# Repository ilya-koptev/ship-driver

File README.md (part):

# ship-driver

`ship-driver` — самодельный драйвер корабельной шины для контроллеров **Wiren Board**. Он берёт
под себя все четыре LoRa‑передатчика (`/dev/ttyMOD1..4`) — это четыре независимых равнозначных
канала. На каждом работает своя копия одного и того же «автомата корабля»: опрашивает борт по
Modbus (модули `pwm8a04` на адресах 11/12/13 и ИБП `WB‑UPS‑v3` на адресе 10), подмешивает в шину
команды плеера DFPlayer, ведёт машину режимов, держит расписание опроса и снижает ток заряда,
когда батарея греется. Всё, что происходит на борту, видно в MQTT — как устройства `boat1..4`.

Кроме кораблей драйвер обслуживает **беспроводные зарядные станции** `charger1..N`: включает реле
передатчика и магнитов фиксации, следит за током передатчика. С зарядками он общается по Modbus
RTU через TCP‑шлюз (EBYTE serial server) — отдельно от корабельной LoRa‑шины.

На корабельной шине он заменяет собой штатные `wb-mqtt-serial` и `rs485-arbiter`.

**Дальше — два больших раздела, под две разные задачи:**

- **[🛰 Удалённое управление по MQTT](#-удалённое-управление-по-mqtt)** — если вы управляете
  кораблём и зарядками из стороннего софта или с дашборда. Здесь только топики, контролы и
  команды; в железо вникать не нужно.
- **[🔧 Устройство, монтаж и настройка](#-устройство-монтаж-и-настройка)** — если вы собираете,
  ставите и настраиваете драйвер на контроллере: как он устроен, как всё подключено, конфиг,
  установка, выпуск релиза.

Полная спецификация MQTT с примерами лежит в **[`MQTT-API.md`](MQTT-API.md)**, а список компонентов
корабля (BOM) — в **[`BUILD.md`](BUILD.md)**.

---

# 🛰 Удалённое управление по MQTT

Здесь собрано всё, что нужно для удалённого управления — про железо и установку можно не думать.

**Как устроены топики.** Прочитать значение можно из `/devices/<устройство>/controls/<контрол>`, а
чтобы отдать команду — пишем в тот же топик с суффиксом `/on`. Устройств три вида: `boat1..4`
(корабли), `charger1..N` (зарядки) и `ship_setup` (проводная преднастройка — она относится к
разделу настройки).

## Корабли `boat1..4`

Устройство `boatN` появляется **только для реально подключённых каналов** — там, где есть порт
`/dev/ttyMODn` и LoRa‑модем отвечает. Состав борта всегда один и тот же: 4 мотора и 5 огней. Пока
канал не на связи (режим SEARCH) или выключен (OFF), на дашборде видны только `enabled`, `mode` и
`ship_number` — остальные контролы прячутся и возвращаются, как только борт выходит на связь.

| Контрол | Доступ | Назначение |
|---|---|---|
| `enabled` | зап. | канал вкл/выкл (1/0) |
| `mode` | чт. | текущий режим (см. ниже) |
| `battery_current` / `battery_voltage` / `battery_temperature` / `charge_level` | чт. | телеметрия ИБП |
| `input_voltage` | чт. | входное напряжение ИБП, В (опрос 5 с, вместе с током) |
| `rssi` / `comms_errors` / `link_quality` | чт. | качество LoRa‑связи активного борта: RSSI (дБм), промахов чтения за 5 мин, % успешных чтений |
| `link_score` | чт. | **общая оценка связи 0…100** — свёртка потерь, качества, сигнала и задержки в одно число (см. «Оценка связи») |
| `read_failures` | чт. | **реально потерянные чтения** за 5 мин — отказы после всех повторов (в отличие от `comms_errors`, где считается каждая попытка) |
| `err_timeout` / `err_frame` | чт. | подпись отказов за 5 мин: «не пришло ни байта» (потерян пакет) против «обрывок / чужой кадр / битый CRC» (фрейминг, тайминги) |
| `course` / `roll` / `pitch` | чт. | углы борта, ° — курс (−180…180), крен, дифферент (датчик считает их сам) |
| `gyro_x` / `gyro_y` / `gyro_z` | чт. | угловые скорости, °/с (`gyro_z` = скорость поворота по курсу) |
| `accel_x` / `accel_y` / `accel_z` | чт. | ускорения в системе борта, g (в них входит и проекция силы тяжести) |
| `mag_x` / `mag_y` / `mag_z` | чт. | магнитометр, сырые единицы — по ним видно искажения поля (моторы, магниты площадки) |
| `q0` … `q3` | чт. | кватернион ориентации (единичный) — для расчётов без разрывов и вырождений |
| `sensor_temp` | чт. | температура датчика, °C |
| `retry_fixed` / `lat_p95` | чт. | промахов, вылеченных повтором, и латентность чтения p95 (мс) |
| `back_left` / `front_left` / `back_right` / `front_right` | зап. | моторы (Back/Front × Left/Right), **0–100 делений газа**: 0 = выход снят, 1 = холостой (1000 мкс), 100 = полный (2000 мкс). Дробные принимаются |
| `nav_lights` / `deck_lights` / `cabin_light1` / `cabin_light2` | зап. | свет, 0–100 % |
| `morse_lamp` | зап. | **переключатель** морзянки: 1 — гонять текст по кругу, 0 — погасить |
| `mp3_track` | зап. | плеер: 0 = стоп, 1–15 = трек |
| `mp3_volume` | зап. | плеер: громкость 0–30 |
| `ship_number` | зап. | номер корабля (= LoRa‑адрес) — переключает канал на этот корабль и делает **полную реинициализацию** (холостой + переарм ESC, газ прежнего борта не наследуется) |

Частоты ШИМ, тока заряда и параметров LoRa (канал, air‑rate, мощность) на дашборде `boatN` нет —
всё это живёт в конфиге контроллера.

### Газ задаётся частотой, а не скважностью

Скважность модуль pwm8a04 принимает только целыми процентами, поэтому при 400 Гц шаг
импульса был 25 мкс — на четырёх моторах это заметные ступеньки хода. Теперь скважность
моторных каналов постоянна (`motor_duty`, 60 %), а газ несёт **частота**: импульс =
`motor_duty` · 1e4 / f. Деления 1…100 это 600…300 Гц и 10.1 мкс на деление; дробные
значения принимаются, железный предел около 2.4 мкс.

Ход ползунка **нелинейный**. Деление 1 — холостой (1000 мкс, ESC взведён, вал стоит),
деление 2 — `pulse_start_us` = 1047 мкс, **измеренная точка страгивания**, дальше до
`pulse_top_us` идёт степенная кривая `x**throttle_gamma`. При `gamma` = 1.5 шаг растёт от
1 мкс у страгивания до 15 мкс у полного газа, и рабочая зона до 1400 мкс занимает половину
ползунка (51 деление) вместо 37 при линейной шкале. `gamma` = 1.0 возвращает линейную.

Круче 1.5 идти бессмысленно: шаг импульса опускается ниже 1.67 мкс, которые железо различает
у холостого, и деления начинают давать одну и ту же частоту — ползунок растёт, управление нет.

Точка страгивания **измерена**, а не оценена: стенд 25.08 без винтов — на 1037 мкс один вал
дёргается (зацепление, не вращение), на 1042 крутятся два, на 1048 все четыре. Прежде деления
2…14 лежали внутри мёртвой зоны и не давали ничего. Разрыв между делениями 1 и 2 намеренный:
это стык «стоит / пошёл», дробные значения между ними смысла не имеют.

Оговорка: пороги четырёх моторов разъехались примерно на 10 мкс, поэтому у самого низа шкалы
два движителя тянут, а два ещё нет — на минимальном газу катер будет уводить. Пол общий на все
каналы; свой пол на канал это вылечило бы, но выбран общий.

### Датчик курса: «его нет» — только про ни разу не ответивший

Такой вывод драйвер делает **только** про датчик, который не ответил ни разу на этом
борту (`sensor_giveup` попыток, по умолчанию 10). Если он отвечал хоть раз — значит
стоит, и при отказах чтения показывается обычная ошибка `meta/error="r"`, а опрос
продолжается.

Признанный отсутствующим переспрашивается раз в `sensor_retry_s` (по умолчанию 60 с) и
**возвращается сам**, сняв пометку. Одна транзакция в минуту ничего не стоит.

Зачем так: 25.08 драйвер объявил отсутствующим датчик, отвечавший минутой раньше —
хватило трёх потерянных кадров подряд при RSSI −57 (чтение идёт без повтора, `tries=1`,
чтобы не занимать канал, поэтому потерянный кадр = неудача). Опрос выключился через 48 с
после старта, и плашка курса 26 минут горела красным с замороженными значениями. Вывод
был сильнее данных, порог низким, а отказ необратимым — исправлено всё три.

### Останов газа идёт через холостой, а не снятием сигнала

Деление 0 снимает сигнал совсем, а регулятор не может отличить «сигнала нет» от
«оборвался провод» — поэтому он выключается не по команде, а по своему
**failsafe-таймауту**, секундами позже. Наблюдение 25.08: после сброса в 0 вал
продолжал вращаться, при этом отказов записи скважности в журнале не было ни одного,
то есть запись проходила и дело было не в ней.

Поэтому останов двухшаговый:

1. сразу выдаётся **холостой импульс** (`motor_duty` на частоте холостого) — это явная
   команда «минимум», регулятор исполняет её немедленно и вал встаёт;
2. через `stop_idle_s` (по умолчанию 1 с) выход гасится совсем, и этот шаг
   **подтверждается чтением** регистра — «записал» и «стало нулём» это разные
   утверждения. Не подтвердилось — повтор до `stop_tries` раз.

Если подтвердить так и не удалось, в журнал идёт `ОСТАНОВ НЕ ПОДТВЕРЖДЁН`, на контроле
выставляется `meta/error="w"`, а мотор **остаётся на холостом импульсе**: выход не снят,
но вал стоит. Это безопаснее, чем настаивать на снятии сигнала.

### Морзянка на световом канале

Канал `morse_lamp` — **переключатель**, а не ползунок яркости. Включённый гоняет по кругу
текст из конфига, выключенный гасит лампу и возвращает каналу штатные 400 Гц.

Символ кодируется **шириной импульса** при низкой частоте: частота ставится один раз,
дальше на каждый символ идёт одна запись скважности. Форму вспышки держит сам модуль,
поэтому дрожание радиоканала сдвигает момент начала символа, но не портит его длину —
а если гонять частоту, на символ уходило бы две записи вместо одной.

По умолчанию: 2 Гц (период 500 мс), точка = скважность 20 (вспышка 100 мс), тире =
скважность 60 (300 мс), текст `AHOY`, цикл 22.5 с. Всё в `main.morse`:
`channel`, `text`, `hz`, `dot`, `dash`, `letter_gap`, `word_gap`, `cycle_gap`
(паузы — в периодах). Латиница и цифры; чего нет в таблице, пропускается.

**Минимум частоты у pwm8a04 — 1 Гц**, проверено записью и обратным чтением 25.08;
значение 65535 модуль записывать отказывается.

Такт даёт общий цикл канала (холостой шаг 0.05 с) — отдельного потока нет. Поэтому
телеметрия может сдвинуть начало символа на свою длительность, но не его ширину.

Полная реинициализация борта (новый корабль или ребут модуля) **гасит морзянку**: её
включали для прежнего борта, и продолжать мигать на новом было бы неверно. После
реконнекта без потери питания она продолжается, сама переставив свою частоту.

### Пол шкалы мерится на каждой установке

`pulse_start_us` — импульс на делении 2 — **переносу между установками не подлежит**.
На стенде без винтов вал шёл с 1047 мкс, а на борту 9 под нагрузкой деления 2…12 дали
ровную полку по току АКБ: мотор крутится на своих минимальных оборотах, и газ на них
не влияет. Рост начинался с 1080 мкс, туда и поставлен пол — полка исчезла, ток растёт
с деления 2 монотонно.

Мерить: `tools/thr-current.py --motor back_left` — ступенчатый проход газа с замером
`battery_current`. Ток объективнее глаз: пока вал стоит, ESC потребляет только на себя.
По одному мотору за прогон, иначе ток не отнести к движителю. `tools/thr-start.py` делает
то же на стенде, где тока нет, — подаёт кандидатов и ждёт, что вал увидят глазами.

Скрипты берут кривую **из конфига драйвера**, а не помнят числами: 25.08 версия с
зашитым полом печатала неверные импульсы сразу после его сдвига.

Порядок записи при смене частоты обязателен: **скважность 0 → частота → рабочая
скважность**. Иначе новая частота ложится на старую скважность и даёт выброс импульса —
на стенде так получился лишний пуск на 1675 мкс. Одиночная команда газа этого не требует:
рабочая скважность уже стоит, меняется только частота (один кадр, задержка как прежде).

Частота вне рабочей полосы означает «модуль потерял питание и вернулся к заводским
1000 Гц» → полная реинициализация с переармом ESC. Отказ идёт в безопасную сторону:
заводская частота выше полосы, значит импульс слишком короткий и моторы стоят.

**Конфиг допускает строки-комментарии `//`.** Раньше не допускал: `json.load` на них
падал, драйвер молча уходил в дефолты и печатал только невнятное `conf load err`.
Снимаются строки, которые целиком комментарий; `//` внутри значения остаётся.

```sh
mosquitto_pub -t /devices/boat1/controls/front_right/on -m 50   # мотор перёд-право = 50%
mosquitto_pub -t /devices/boat1/controls/nav_lights/on  -m 100  # ходовые огни = 100%
mosquitto_pub -t /devices/boat1/controls/mp3_track/on   -m 3    # играть трек 3
mosquitto_pub -t /devices/boat2/controls/ship_number/on -m 23   # канал 2 -> корабль №23 (сразу)
mosquitto_sub -t /devices/boat1/controls/mode                   # текущий режим
```

### Режимы (`mode`)

| Режим | Когда | Что делает |
|---|---|---|
| **SEARCH** | корабль не на связи | непрерывно зондирует эфир; поймал ответ → инициализация → рабочий режим |
| **SAILING** | пришла любая команда управления | сбрасывает таймер 30 с (команды плеера режим не меняют) |
| **CHARGING** | 30 с без команд и ток батареи > 0 | заряд идёт максимально быстро, но под контролем температуры (см. «Тепловой регулятор») |
| **IDLE** | 30 с без команд и ток ≤ 0 | дрейф на батарее |
| **OFF** | `enabled = 0` | порт закрыт, эфир не трогается |

Из любого режима драйвер уходит в **SEARCH**, как только корабль перестаёт отвечать (два промаха
подряд). По умолчанию все 4 канала включены; и состояние вкл/выкл, **и заданный `ship_number`**
переживают перезагрузку контроллера.

### Номер корабля (`ship_number`)

У всех кораблей на одной радио‑частоте Modbus‑адреса одинаковые, поэтому на канале в каждый момент
можно разговаривать только с одним бортом — какой именно, задаёт **номер корабля** (он же
LoRa‑адрес приёмника). Стоит записать новое значение в `ship_number`, и канал мгновенно
переключается на нужный корабль: драйвер прописывает адрес в модем, берёт из конфига разводку
моторов и света именно этого корабля и через короткий SEARCH **инициализирует его заново** (частота
ШИМ и холостой газ). Раньше без этого шага при двух кораблях на одном канале второй мог не получить
`FREQ` и холостой газ — и тогда его моторы не заводились, хотя свет работал.

### Матрица опроса (период чтения телеметрии)

| Параметр | SEARCH | SAILING | IDLE | CHARGING |
|---|---|---|---|---|
| Ток батареи + вх. напряжение ИБП | ~0.8 с | 2 с | 5 с | 5 с |
| Температура АКБ | — | 60 с | 60 с | 10 с |
| Процент заряда | — | 60 с | 60 с | 20 с |
| Моторы + свет (обратная сверка, блочное чтение) | — | 30 с | 60 с | 30 с |
| Проверка частоты ШИМ (авто-восстановление 400 Гц, поиск молчащего модуля) | — | 10 с | 10 с | 10 с |

А вот команды управления (моторы, свет, плеер) применяются сразу же, в обход расписания.

**Надёжность чтения.** Связь идёт по радио (LoRa), одиночные потери пакетов случаются. Поэтому каждое чтение при промахе **повторяется** (`read_tries`, по умолчанию 2 попытки) — транзиентный сбой маскируется в том же цикле, значение остаётся свежим. «Ошибка чтения» (`meta/error = "r"`, красный контрол на дашборде) остаётся только для реальной потери связи. **Ошибка записи** помечается так же, но кодом `w`: результат каждой записи проверяется, и команда, не дошедшая до модуля, больше не публикуется как применённая — раньше оператор видел газ, которого в железе нет. Качество линка видно в контролах `rssi` (сила сигнала), `comms_errors` (сырых промахов за 5 мин) и `link_quality` (% успешных чтений) — они отражают тот корабль, что сейчас на канале.

В SEARCH (борт не на связи) неответ — это **не** ошибка связи, а «борта здесь нет»: такие зондирования не повторяются, не попадают в счётчики и не пишутся в журнал.

### Тепловой регулятор заряда

**Задача — зарядить как можно быстрее, не упираясь в аппаратную защиту.** У WB‑UPS‑v3 заряд
блокируется при температуре батареи **выше +50 °C**. Если просто выставить максимальный ток
(2000 мА, это 0.77C для батареи 2×2600 мА·ч), борт нагревается до порога примерно за полчаса,
защита рвёт заряд, дальше он идёт рывками — и греет батарею впустую.

Поэтому драйвер сам управляет током: держит температуру у **48 °C** (порог с запасом 2 °C) и
отдаёт ровно столько тока, сколько борт способен рассеять. Холодный борт заряжается на полных
2000 мА, по мере нагрева ток плавно снижается до равновесного.

**Как считает.** Процесс инерционный, поэтому регулировать по текущей температуре поздно — она
успеет проскочить. Регулятор смотрит на **прогноз**: `t + скорость_роста × горизонт` (по умолчанию
5 минут). Это и есть D‑член, но в понятном виде — «где будем через 5 минут». Дальше обычный ПИ по
этой ошибке, с анти‑виндапом (в насыщении интеграл не копится) и жёсткой страховкой: при
`t ≥ цель + 1 °C` ток сразу падает до минимума.

Скорость роста считается **методом наименьших квадратов по окну 240 с** (`slope_win_s`), а не
разностью крайних точек. Это важно: датчик отдаёт температуру ступеньками ~0.1 °C, и на разности
двух точек оценка скакала ±0.3 °C/мин — после умножения на горизонт и `Kp` ток мотался
300 ↔ 1100 мА, а настроечный регистр 18 писался сотнями раз в сутки (283 записи за 10.08).
МНК по широкому окну убирает это на порядок: по модели с квантованием — 12 записей в час вместо 120,
и заодно чуть точнее держится цель.

Ток пишется в модуль **редко** — только при изменении больше `deadband_ma` (40 мА) и не чаще
`min_write_s` (20 с): регистр 18 настроечный, незачем дёргать его каждые 10 секунд.

Текущая уставка видна в контроле `charge_setpoint` (мА) и пишется в историю, так что работу
регулятора можно посмотреть графиком.

Проверено на модели, снятой с наших же замеров (нагрев +1.1 °C/мин при 2000 мА, равновесие
≈ 680 мА при 24 °C): в норме выходит на 48.0 °C без колебаний; при жаре +32 °C сам снижает до
≈ 450 мА, на холоде +15 °C поднимает до ≈ 930 мА. Худший случай (медленный датчик, запаздывание
60 с) — пик 48.9 °C, то есть на 1.1 °C ниже аппаратной отсечки.

Настройки — в **«Основное → Заряд → Тепловой регулятор»**: целевая температура, минимальный ток,
`Kp`, `Ki`, горизонт прогноза, порог и частота записи. Выключается галочкой (тогда драйвер просто
держит максимальный ток, как раньше).

### Оценка связи `link_score` (0…100)

Смотреть на пять сырых счётчиков одновременно неудобно: RSSI может быть отличным, а данные при этом
теряться (и наоборот — слабый сигнал ещё не значит проблему, если ретрай всё вытягивает). Поэтому
драйвер сворачивает их в **одно число 0…100**, где 100 — идеал. Считается там же, где и счётчики
(в конце каждого цикла опроса тока), поэтому лишнего обмена по шине не создаёт.

**Как получается оценка.** Каждый показатель переводится в свою подоценку 0…100, пороги взяты из
измеренной нормы борта (RSSI ≈ −53 дБм, `link_quality` ≈ 96.6 %, `read_failures` = 0, `lat_p95` ≈ 117 мс):

| Показатель | Что означает | Как переводится в баллы | Вес |
|---|---|---|---|
| `read_failures` | **реальная потеря данных** (отказ после всех повторов) | `100·e^(−n/12)`: 0 → 100, 1 → 92, 2 → 85, 5 → 66, 10 → 43 | 0.45 |
| `link_quality` | доля удачных попыток чтения | 100 % → 100, 95 % → 75, 90 % → 50, ≤ 80 % → 0 | 0.25 |
| `rssi` | запас по уровню сигнала | −50 дБм → 100, −75 → 60, −90 → 25, ≤ −100 → 0 | 0.20 |
| `lat_p95` | **рост** задержки (не сама величина) | ≤ 250 мс → 100, 400 → 75, 600 → 42 | 0.10 |

Две калибровки специально «мягкие», и вот почему (проверено на живых данных 08.08):

- **Потери.** Одна неудачная пара попыток за 5 минут — это ≈ 0.3 % чтений (их в окне ~370), и значение
  обновится через 5 с следующим циклом. Первая версия шкалы (`e^(−n/3)`) роняла индекс на 13 пунктов
  за единственную потерю, из‑за чего 39 % времени он висел ниже 90 при полностью здоровом канале.
  Теперь тревога наступает там, где потери **копятся**, а не от единичной.
- **Задержка.** Базовая `lat_p95` зависит от состава борта: без датчика ≈ 95 мс, с инклинометром
  ≈ 220 мс (длинное блочное чтение 33 регистров). Штраф с порога 100 мс означал бы вечный минус
  ~24 пункта просто за наличие датчика, поэтому штраф считается только **выше 250 мс** — то есть за
  реальный рост задержки.

Дальше — взвешенное среднее, **плюс ограничение сверху**: итог не может превышать «оценку потерь + 20».
Это главное свойство формулы — **реальные потери всегда тянут индекс вниз**, даже когда сигнал
отличный. Иначе борт у самого причала (−40 дБм) показывал бы «отлично», теряя при этом данные.

Если какого‑то показателя ещё нет (например, RSSI до первого успешного пакета), его вес просто
исключается из суммы — оценка считается по оставшимся.

**Как читать:** ≥ 90 — отлично, 75…90 — хорошо, 50…75 — слабо, < 50 — плохо. Для ориентира при
нынешней калибровке: здоровый линк (потерь нет, `link_quality` ≈ 98, RSSI −45) даёт ≈ 97–98;
одна потеря за 5 минут — 94; две — 91; провал в «слабо» наступает при 5+ потерях за окно.

Сырые счётчики никуда не деваются: они по‑прежнему в MQTT и в истории, и именно по ним разбираются
причины, когда индекс проседает. `link_score` — это «светофор», а не замена диагностике.

**Блочная запись (Modbus func 16).** Регистры скважности внутри модуля идут подряд, поэтому драйвер пишет их **одним кадром на модуль**: оба мотора модуля — одна транзакция вместо двух, инициализация борта — 6 транзакций вместо 18. Поддержка проверяется автоматически при первой блочной записи; если модуль func 16 не понимает, драйвер молча откатывается на поштучную запись (в журнале будет строка об этом).

**Диагностика природы отказов.** Не всякий промах — «плохое радио». Драйвер классифицирует каждую неудачную попытку: `err_timeout` (не пришло ни байта — так выглядит потерянный пакет) и `err_frame` (обрывок кадра, чужой slave/func, битый CRC — так выглядят тайминги и мусор в буфере). Плюс `retry_fixed` (сколько промахов вылечил повтор), `lat_p95` (латентность) и `read_failures` (отказы после всех попыток = реальная потеря данных). Каждый промах пишется в журнал строкой с типом, адресом, мгновенным RSSI и полученными байтами — этого достаточно, чтобы отличить эфир от протокола, не выходя на воду.

**Мощность передатчиков и взаимное глушение (важно для нескольких бортов).** Береговые модемы стоят рядом, поэтому передатчик одного канала **глушит приёмник** соседнего независимо от расстройки по частоте: полезный сигнал с борта приходит примерно −55 дБм, а сосед светит в сантиметрах. На 22 дБм это давало ~6 % промахов на рабочем канале, стоило трём другим каналам работать. На **10 дБм глушение исчезает полностью** (проверено A/B: 0 промахов при работающих соседях против 36 за 15 минут на 22 дБм), а запас над чувствительностью остаётся огромным. Поэтому по умолчанию в конфиге стоит `power: 10`; поднимать стоит только если не хватает дальности, и тогда — вместе с разносом антенн (≥ 20–30 см) и распределением активных бортов по самым далёким друг от друга каналам (14 и 19).

Если промахи всё же окажутся «фреймингом», есть параметр **«Пауза перед транзакцией, мс»** (`tx_gap_ms`, по умолчанию 0): даёт модему домолчать и переключить TX→RX перед следующим запросом.

## Зарядки `charger1..N`

Береговые беспроводные зарядные станции. Каждая появляется в MQTT отдельным устройством `charger<N>`
(с заголовком `Charger 1…N`) и управляется теми же командами с суффиксом `/on`.

| Контрол | Доступ | Назначение |
|---|---|---|
| `transmitter` | зап. | передатчик зарядки вкл/выкл (1/0) |
| `magnets` | зап. | магниты фиксации судна вкл/выкл (1/0) |
| `transmitter_current` | чт. | ток передатчика, А |
| `charge_link` | чт. | **связь катушек, %** — сколько из запрошенного тока реально доходит до батареи |

```sh
mosquitto_pub -t /devices/charger1/controls/transmitter/on -m 1   # передатчик вкл
mosquitto_pub -t /devices/charger1/controls/magnets/on     -m 1   # магниты вкл
mosquitto_sub -t /devices/charger1/controls/transmitter_current   # ток передатчика
```

> При старте драйвер ничего не переключает — он лишь **показывает** фактическое состояние реле зарядки.

**Индикатор посадки `charge_link`.** Показывает, насколько хорошо борт сел на площадку, — по
**просадке входного напряжения**, а не по току. При нормальной передаче `input_voltage` держится у
холостых ≈ **12.7 В** и садится примерно на **0.35 В на каждый ампер** заряда; при кривой посадке
проваливается на 2 В и больше. Индикатор: 100 % при нулевом недоборе, 0 % при недоборе 2 В.

Почему не «фактический ток / уставка» (так было в 1.9.20): когда батарея заряжена, ИБП сам перестаёт
брать ток — **борт при этом продолжает питаться от площадки** — и метрика по току показывала бы
«плохую связь» там, где всё в порядке. Просадка от состояния батареи не зависит.

Проверено на 9 днях истории: нормальные сессии дают недобор **0.03…0.26 В** (индикатор 89…94 %),
плохие — **2.0…2.2 В** (0…13 %). Сходится и спорный случай: полная батарея при кривой посадке
(Vbat 8.04, Vin 9.72) честно даёт **0 %**, а полная батарея без нагрузки (Vin 12.69) — **100 %**.

Модель линка настраивается в конфиге (`charge.link`): холостое напряжение, сопротивление передачи,
недобор, соответствующий нулю, и окно сглаживания. Если борта на паду нет (`input_voltage` ≤ 5 В)
или передатчик выключен — ячейка помечается как «нет данных».

---

# 🔧 Устройство, монтаж и настройка

Все настройки лежат в одном файле **`/etc/ship-driver.conf`** (JSON). Проще всего править его прямо
из веб‑интерфейса WB: **Настройки → Конфигурационные файлы → «Ship Driver»** (форму рисует схема
`wb-mqtt-confed`). Сохранили — и сервис сам перезапустится.

## Принцип работы

Корабли на одном канале драйвер различает по **номеру корабля** (это LoRa‑адрес приёмника, см.
[«Номер корабля»](#номер-корабля-ship_number)). При старте он приводит модем в соответствие с
конфигом — конфиг тут главный (**config‑authoritative**): читает регистры и, если они разошлись,
переписывает целиком (адрес, канал, air‑rate, мощность и reg5). Адрес берёт из сохранённого
`ship_number`, а если его нет — из конфига; канал, air‑rate и мощность — всегда из конфига. Сам
адрес можно менять на лету, контролом `ship_number`.

Корабль считается **онлайн**, если ответило хотя бы одно из четырёх Modbus‑устройств: либо UPS по
току (адрес 10), либо любой из pwm8a04 по регистру частоты (11/12/13). Поэтому борт находится
**даже при выключенном UPS** — по pwm; просто телеметрия батареи будет пустой.

Как только канал выходит в онлайн, драйвер решает по состоянию pwm‑модулей, что делать:
- модули **ребутнулись** (частота слетела с 400) **или** это была **смена корабля** → полная
  инициализация: мощность 0 → частота ШИМ 400 → моторы в холостой (40) + свет из конфига (взвод ESC);
- модули **живы** (держат 400), а был лишь короткий провал связи → драйвер **не сбрасывает газ**, а
  восстанавливает последний заданный (resume) — чтобы борт на ходу не «дёргался» из‑за радио‑икоты.

Уход в оффлайн (после нескольких промахов подряд) и возврат на связь теперь **пишутся в журнал**
(причина + длительность разрыва). Состояние вкл/выкл каналов и `ship_number` хранится в
`/etc/ship-driver-state.json`.

**Самопроверка частоты ШИМ** (группа `freq_check`, каждые 10 с). Драйвер читает частоту каналов
pwm8a04, и если она слетела в дефолт (не 400 Гц) — значит модуль перезагрузился, обычно от просадки
питания на броске тока моторов. Такой модуль остаётся «онлайн», но его ESC уже не взведены, поэтому
одной частоты тут мало: моторы всё равно не заведутся (а свет при этом работает). Поэтому драйвер
**сам гонит борт в оффлайн и инициализирует заново** — частота 400, взвод ESC, холостой газ (в
журнале: `freq drift … форсирую реинициализацию`). Проверка частая (раз в 10 с) как раз затем, чтобы
такой браунаут лечился за секунды и без ручного вмешательства — без ухода в SEARCH и смены `ship_number`.

**Модуль, который не отвечает совсем** — случай опаснее дрейфа частоты, и разбирается отдельно.
Раньше неответ в `freq_check` просто пропускался: навсегда пропавший модуль не поднимал ничего,
кроме красной подписи на своих контролах. Теперь драйвер считает неответы по каждому адресу и
после `lost_misses` подряд (по умолчанию 6, около минуты) объявляет **аварию**: пишет в журнал
`ОШИБКА: модуль N не ответил … Неуправляемы: …` с перечислением каналов и **гасит остальные
моторы в холостой** — идти с отказавшим модулем нельзя. Повторно не дёргает, пока модуль не
ответит. Случай 24.08 на борту 9: pwm8a04 с адресом 11 замолчал в 14:07, правые моторы и
навигационный свет были неуправляемы 7.5 часов, борт продолжал слушаться левых моторов, и
единственным признаком были три красные подписи.

⚠ Один номер корабля на двух **включённых** каналах — это два разных радиолинка на один адрес,
и диагностика становится неоднозначной. Драйвер предупреждает об этом при старте строкой в журнале.

Обратную сверку моторов и света (что реально записано в модуле против того, что мы задавали) драйвер
делает **блоком** — один Modbus‑обмен на модуль (регистры 112–114), а не по каналу за раз. Если вычитанное расходится с заданным, **хозяин — драйвер**: он переписывает своё значение в модуль, а не публикует железное в контрол. Иначе получается разъезд «ползунок показывает газ, режим IDLE, борт стоит».

## Датчик курса (WT901C485 / JY‑901)

На борту может стоять инклинометр **WitMotion WT901C485** — он висит на той же бортовой шине, что УПС и pwm‑модули (по умолчанию Modbus‑адрес **14**, 9600). Модуль сам сводит акселерометр, гироскоп и магнитометр своим фильтром и отдаёт **готовый угол**, интегрировать ничего не нужно: драйвер читает **весь блок `0x34–0x54` одной транзакцией** (33 регистра, ~220 мс): ускорения, гироскоп, магнитометр, углы, температуру и кватернионы — и публикует их отдельными контролами. На дашборд выведен только **`course`**; остальное копится в истории для разбора.

Настройки — **в блоке своего корабля** (Настройки → Ship Driver → **Корабли → Список кораблей → Корабль №N → «Датчик курса»**, сразу после «Моторов»), потому что датчик стоит не на каждом борту: включение, Modbus‑адрес и **инверсия** (если датчик смонтирован зеркально/вверх ногами, вращение читается в обратную сторону). Период опроса задаётся в матрице опроса полем «Курс»: по умолчанию 1 с в SAILING и 10 с в остальных режимах.

Датчик стоит не на всех бортах, поэтому опрос **самоотключается**: после трёх неудач подряд драйвер перестаёт его дёргать для этого борта и пишет строку в журнал (чтобы не плодить ложные ошибки чтения). Проверка возобновляется при инициализации борта — то есть при смене `ship_number` или новом выходе на связь.

> На дашборде показан только курс — для управления остального не нужно; но всё сырьё пишется в историю, чтобы потом разобрать динамику (разгон, рыскание, искажения магнитного поля). Абсолютная привязка курса к северу требует калибровки магнитометра: рядом BLDC‑моторы и магниты фиксации, они искажают поле, поэтому пока курс отсчитывается от произвольного нуля датчика.

## Подключение света (выходы платы OUT1–OUT5)

На плате пять световых **выходов** `OUT1…OUT5`. Коммутирует их сборка Дарлингтона **ULN2003A**
(U6): это ключи с открытым коллектором — они пропускают «втекающий» ток, то есть замыкают выход на
землю. На входы ULN приходит ШИМ 5 В с каналов `pwm8a04`. Нагрузку (лента или лампа) вешают между
**общим +12 В платы** и нужным выходом `OUTx`; «+12 В» выведено на тех же разъёмах рядом с
выходами, а общий вывод ULN (COM) заведён на +12 В — для защитных диодов.

Весь свет разведён через **три модуля `pwm8a04`** (Modbus‑адреса `a11 / a12 / a13`) и **два выходных
разъёма** платы:

<table>
<thead><tr><th>Контрол (топик)</th><th>Свет</th><th>pwm8a04</th><th>Канал</th><th style="background:#fde047">выход на плате</th></tr></thead>
<tbody>
<tr><td><code>nav_lights</code></td><td>Navigation lights (ходовые огни)</td><td>a11</td><td>ch3</td><td style="background:#fde047">1</td></tr>
<tr><td><code>morse_lamp</code></td><td>Morse signal lamp (прожектор морзе)</td><td>a12</td><td>ch3</td><td style="background:#fde047">2</td></tr>
<tr><td><code>deck_lights</code></td><td>Deck lights (палубные огни)</td><td>a13</td><td>ch1</td><td style="background:#fde047">3</td></tr>
<tr><td><code>cabin_light1</code></td><td>Cabin light 1 (внутренний свет 1)</td><td>a13</td><td>ch2</td><td style="background:#fde047">4</td></tr>
<tr><td><code>cabin_light2</code></td><td>Cabin light 2 (внутренний свет 2)</td><td>a13</td><td>ch3</td><td style="background:#fde047">5</td></tr>
</tbody>
</table>

> ⚡ **Выходы 4 и 5 — сдвоенные:** на каждом параллельно работают **два** ключа ULN, так что они
> тянут примерно **вдвое больший ток** — вешай на них нагрузки помощнее.

**Токи (ULN2003A):**

- Выходы **1–3** (одиночный ключ) — до **~500 мА** длительно (пик 600 мА).
- Выходы **4 и 5** (два ключа параллельно) — до **~1 А**.
- Напряжение нагрузки до 50 В (на плате +12 В); падение на ключе `VCE(sat)` ≈ 1.1–1.6 В (греется).
- **Суммарно по корпусу** мощность ULN ограничена (≈ 1 Вт при 25 °C), поэтому держать все выходы на
  максимуме одновременно нельзя — работает деретинг по числу открытых ключей и по температуре.
  ШИМ со скважностью меньше 100 % снижает средний нагрев.

**Как подключать.** Плюс нагрузки — на **+12 В** платы, минус — на нужный выход. Яркость
регулируется ШИМ 0–100 % через контрол света (`nav_lights` … `cabin_light2`). Мощную нагрузку вешай
на сдвоенные выходы **4/5**, а если и этого мало — ставь внешний MOSFET.

## Зарядные станции — железо

Береговая станция подключена через **шлюз Modbus‑RTU‑over‑TCP** (прозрачный EBYTE serial server,
`host:port`) — отдельно от корабельной LoRa‑шины. Из железа на станции: передатчик беспроводной
зарядки **XKT‑801** и **магниты фиксации** судна. Они сидят на **разных каналах** реле
**WB‑MRM2‑mini** (реле нормально‑замкнутые, поэтому в конфиге для них включена «инверсия»). Ток
передатчика снимается как падение на шунте и измеряется модулем **WB‑MAI6** (ток = напряжение,
делённое на сопротивление шунта).

Станции можно вешать как угодно: несколько на один шлюз (тогда они делят TCP‑соединение) или каждую
на свой; и один WB‑MAI6 может обслуживать сразу несколько станций — по разным входам `IN`. Про
управление по MQTT — см. раздел [«Зарядки `charger1..N`»](#зарядки-charger1n).

## Конфигурация — `/etc/ship-driver.conf`

Редактируется в вебе (**Настройки → Конфигурационные файлы → «Ship Driver»**) или прямо в файле.
Из чего он состоит:

- **Основное:** скорость шины (список), таймаут ответа, ток заряда (тепловую защиту заряда
  делает сам WB‑UPS‑v3, в конфиге её нет), значения инициализации, пределы интерфейса (моторы/трек),
  матрица опроса (+ «таймаут без команд», «промахи до SEARCH», «повторов чтения»), «каналы включены при старте».
- **Радио:** план MOD1–4 — канал / air‑rate / адрес / мощность каждого передатчика.
- **Корабли:** «По умолчанию» (общие `air_rate` + `power`, резервная разводка и датчик) и «Список
  кораблей» — каждый по своему **номеру (= LoRa‑адрес)**: LoRa‑канал, разводка моторов/света
  → ШИМ (адрес + канал) и **свой «Датчик курса»** (есть ли он на борту, его адрес, инверсия).
- **Зарядки:** список зарядных станций. У каждой — свой TCP‑шлюз (`host:port`), выходы реле
  **«Передатчик»** и **«Магниты фиксации»** (адрес реле + канал K + инверсия для NC) и датчик
  тока **WB‑MAI6** (адрес + вход `IN` + сопротивление шунта). Имена устройств — `Charger N`.

Канал LoRa выбирается из списка с частотами; разрешённые ГКРЧ помечены `✓ ГКРЧ`
(CH14/16/17/19), остальные — `⚠ вне ГКРЧ`. Захардкожены: база частоты 850.125 МГц, профиль
E220 (UART 9600, subpkt128, RSSI), макс. громкость, пределы контролов, дефолты дашборда.
RU/ГКРЧ‑каналы: CH14 = 864.125, CH16 = 866.125, CH17 = 867.125, CH19 = 869.125 МГц.

## Дашборд «Ship Setup (RS485‑1)» — преднастройка корабля по проводу

Это MQTT‑устройство `ship_setup` — им прошивают LoRa‑модем корабля через порт `/dev/ttyRS485-1`.
Вручную задаются два поля — **«Номер корабля» (`ship_number`)** и **«LoRa канал» (`LoRa_channel`)**;
всё остальное только показывает состояние и запускает действия:

- `ship_number` / `LoRa_channel` — задаются вручную; `LoRa_address` — дубль номера (чтение);
  `LoRa_freq` и `Band (GKRCh)` — частота и диапазон по выбранному каналу (пересчитываются сразу);
- **«Read»** (`LoRa_read`) — читает 9 байт регистров подключённого модема и показывает все
  декодированные параметры: адрес, канал, air‑rate, мощность, LBT, UART, субпакет, RSSI эфира/в
  пакете, режим TX, WOR, версия, `raw (9 bytes)` + строка `LoRa default` для сравнения;
- **«Write»** (`LoRa_apply`) — пишет в модем заданные номер и канал (полный дамп регистров);
- результат операции (OK/ошибка) — в журнале: `journalctl -u ship-driver`.

По шагам: подключаем корабль к RS485‑1 → переводим его модем в режим **CONFIG** (переключателем на
плате) → задаём «Номер корабля» и «LoRa канал» → жмём **«Write»** (или «Read», чтобы проверить) →
возвращаем модем в **RUN**. После этого канал MODn с тем же каналом и скоростью подхватит корабль.

## Временно отдать шину штатному `wb-mqtt-serial` (напр., для настройки УПС)

**Проще всего — переключателем на дашборде.** Пакет ставит правило wb-rules
(`/etc/wb-rules/ship-bus-switch.js`) с виртуальным устройством **«Драйвер шины корабля»**
(`ship_bus`): там есть переключатель `ship_driver` (включён = работает `ship-driver`, выключен =
`wb-mqtt-serial`) и индикатор того, какой сервис сейчас активен. Логика идемпотентна, поэтому
перезапуск движка wb-rules сервисы не дёргает. Когда драйвер **останавливается** (мы отдаём шину
serial), он сам убирает свои дашборды `boatN` и `Ship Setup` — чистит retained‑топики; а при старте
объявляет их заново.

Можно и вручную, через `systemctl`. Вместе драйвер и `wb-mqtt-serial` работать не могут
(`Conflicts`). Для временного переключения берём `start`/`stop` **без** `enable/disable` — тогда
после перезагрузки сам вернётся `ship-driver`:

```sh
systemctl stop  ship-driver  && systemctl start wb-mqtt-serial   # отдать serial
systemctl stop  wb-mqtt-serial && systemctl start ship-driver    # вернуть драйвер
```

Благодаря `Conflicts` хватает и одной команды — запуска нужного сервиса. А если настройка затянется
и должна пережить перезагрузку, тогда уже `systemctl disable --now ship-driver` / `enable --now wb-mqtt-serial`.

## Установка на контроллер (один раз)

> **Сначала — железо.** Каждый MOD‑слот с LoRa‑модулем надо перевести в конфигурации
> Wiren Board в тип **«LoRa»** (веб: Настройки → Конфигурация Wiren Board → MODx → LoRa).
> Иначе UART слота не поднимется: `/dev/ttyMODn` не откроется (ошибка
> *Could not configure port: Input/output error*), и канал будет считаться отсутствующим —
> дашборд `boatN` попросту не появится.

Перед установкой не помешает обновить систему.

```sh
echo "deb [trusted=yes] https://ilya-koptev.github.io/ship-driver ./" | sudo tee /etc/apt/sources.list.d/ship-driver.list
sudo apt update
sudo apt install ship-driver
```

Что кладётся: сам драйвер `/usr/bin/ship-driver.py`, юнит `/lib/systemd/system/ship-driver.service`,
конфиг `/etc/ship-driver.conf` (это dpkg **conffile**, так что ваши правки переживут обновление) и
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
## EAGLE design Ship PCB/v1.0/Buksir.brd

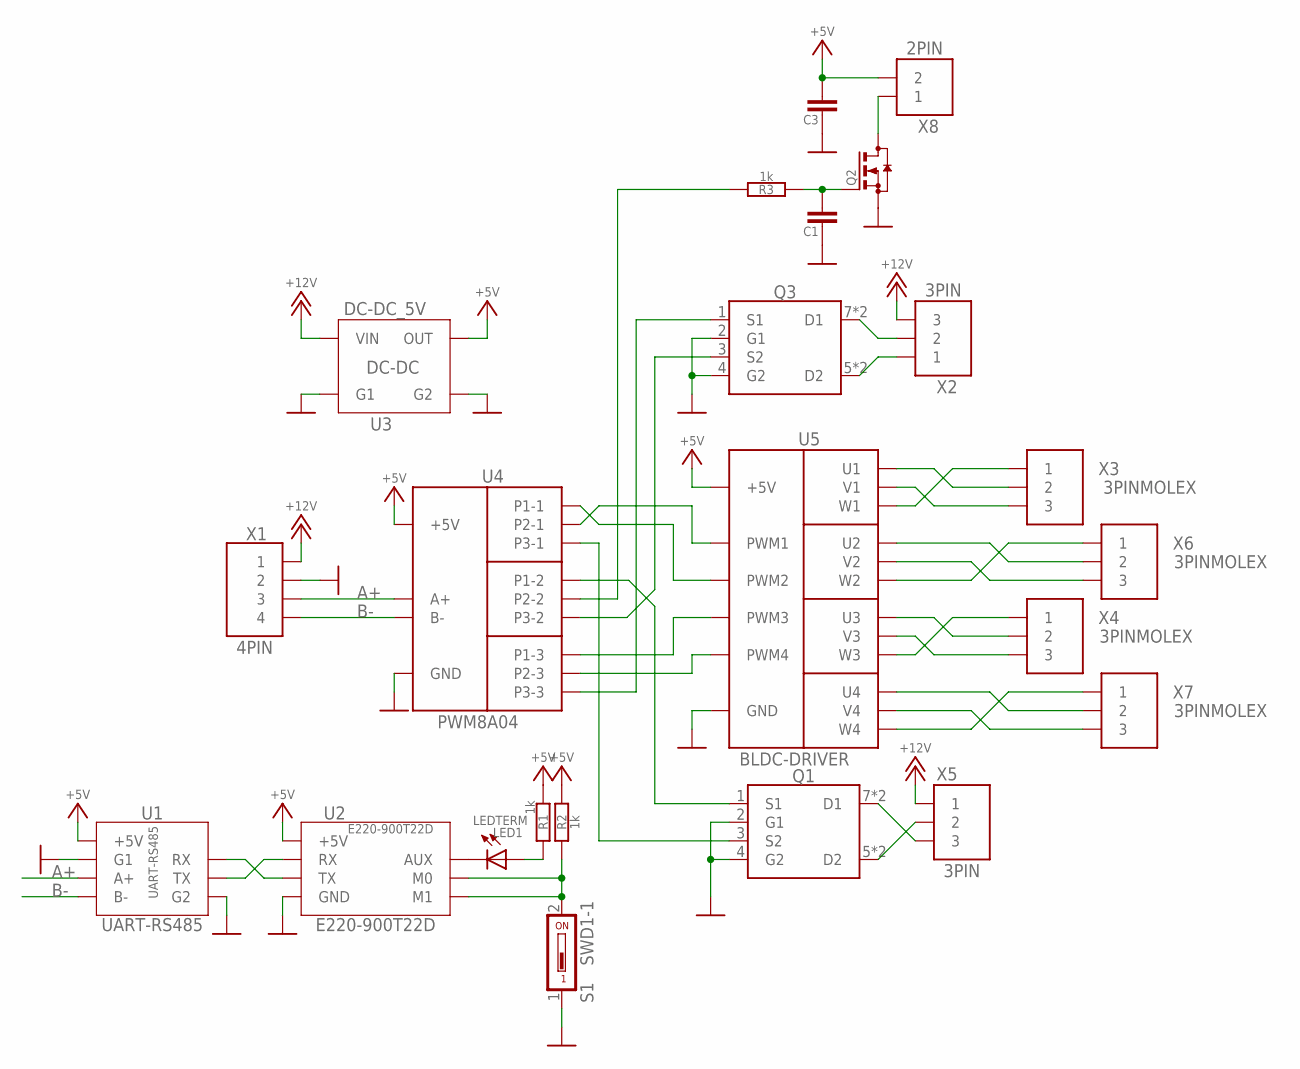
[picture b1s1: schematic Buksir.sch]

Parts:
C1, C3: CAPACITOR1206; C1206
LED1: LEDTERM; LED_TERM
Q1, Q3: NCV8402ADDR2G; SOIC-8
Q2: FET-N; SOT23
R1, R2, R3: 1k; R0805
S1: SWD1-1; DS-01
U1: UART-RS485
U2: E220-900T22D
U3: DC-DC_5V
U4: PWM8A04
U5: BLDC-DRIVER
X1: 4PIN; 4PIN-2.5MM
X2, X5: 3PIN; 3PIN-2.5MM
X3, X4, X6, X7: 3PINMOLEX; 3PIN-MOLEX
X8: 2PIN; 2PIN-2.5MM

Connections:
+5V: C3.2, R1.2, R2.2, U1.VCC (+5V), U2.VCC (+5V), U3.OUT, U4.+V (+5V), U5.B+ (+5V), X8.P$2 (2)
A+: U1.A+, U4.A+, X1.P$2 (3)
B-: U1.B-, U4.B-, X1.P$1 (4)
GND: C1.1, C3.1, Q1.2 (G1), Q1.4 (G2), Q2.2 (S), Q3.2 (G1), Q3.4 (G2), S1.1, U1.G1, U1.G2, U2.GND, U3.G1, U3.G2, U4.GND, U5.B- (GND), X1.P$3 (2)
unnamed: U1.TX, U2.RXD (RX)
unnamed: U1.RX, U2.TXD (TX)
unnamed: LED1.K (C), U2.AUX
unnamed: LED1.A, R1.1
unnamed: R2.1, S1.2, U2.M0, U2.M1
unnamed: Q3.7 (D1), Q3.8 (D1), X2.P$2 (2)
unnamed: Q3.5 (D2), Q3.6 (D2), X2.P$1 (1)
unnamed: Q1.5 (D2), Q1.6 (D2), X5.P$2 (2)
unnamed: U4.P2-3, U5.PWM4
unnamed: Q1.7 (D1), Q1.8 (D1), X5.P$3 (3)
unnamed: U4.P1-3, U5.PWM3
unnamed: U4.P1-1, U5.PWM2
unnamed: U5.U1, X3.P$2 (2)
unnamed: U5.V1, X3.P$3 (3)
unnamed: U5.W1, X3.P$1 (1)
unnamed: U5.W2, X6.P$1 (1)
unnamed: U5.V2, X6.P$3 (3)
unnamed: U5.U2, X6.P$2 (2)
unnamed: U5.U3, X4.P$2 (2)
unnamed: U5.V3, X4.P$3 (3)
unnamed: U5.W3, X4.P$1 (1)
unnamed: U5.U4, X7.P$2 (2)
unnamed: U5.V4, X7.P$3 (3)
unnamed: U5.W4, X7.P$1 (1)
unnamed: U4.P2-1, U5.PWM1
unnamed: Q2.3 (D), X8.P$1 (1)
unnamed: C1.2, Q2.1 (G), R3.1
unnamed: R3.2, U4.P2-2
P1-2: Q1.1 (S1), U4.P1-2
P3-1: Q1.3 (S2), U4.P3-1
P3-2: Q3.3 (S2), U4.P3-2
P3-3: Q3.1 (S1), U4.P3-3
V_IN: U3.VIN, X1.P$4 (1), X2.P$3 (3), X5.P$1 (1)

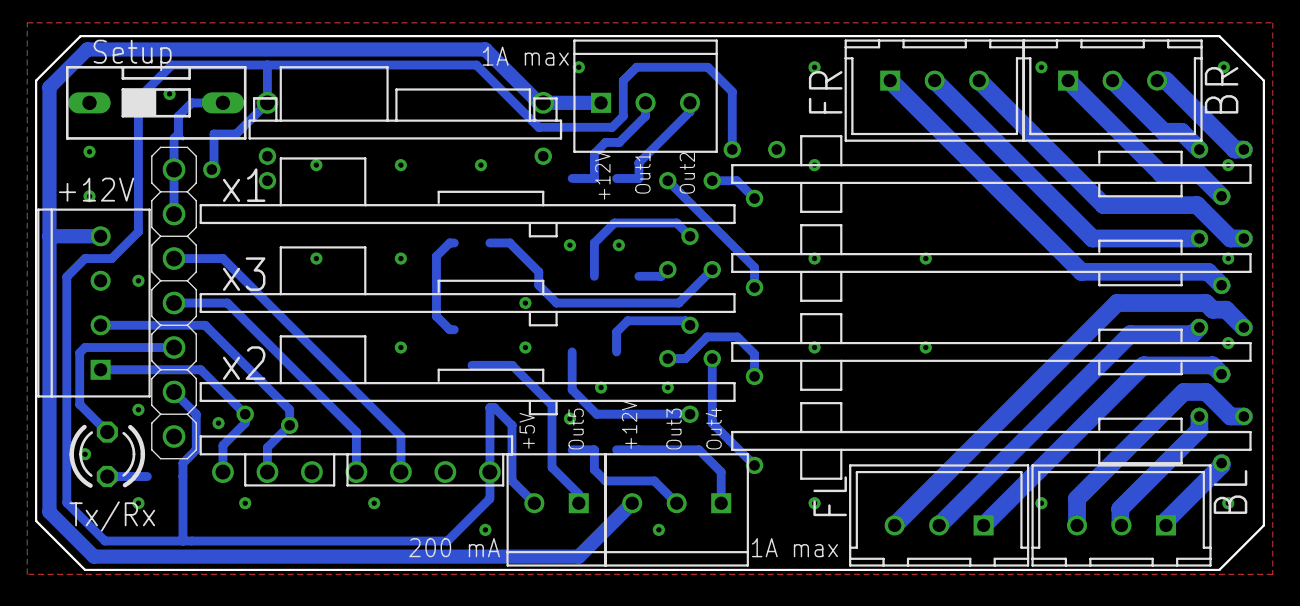
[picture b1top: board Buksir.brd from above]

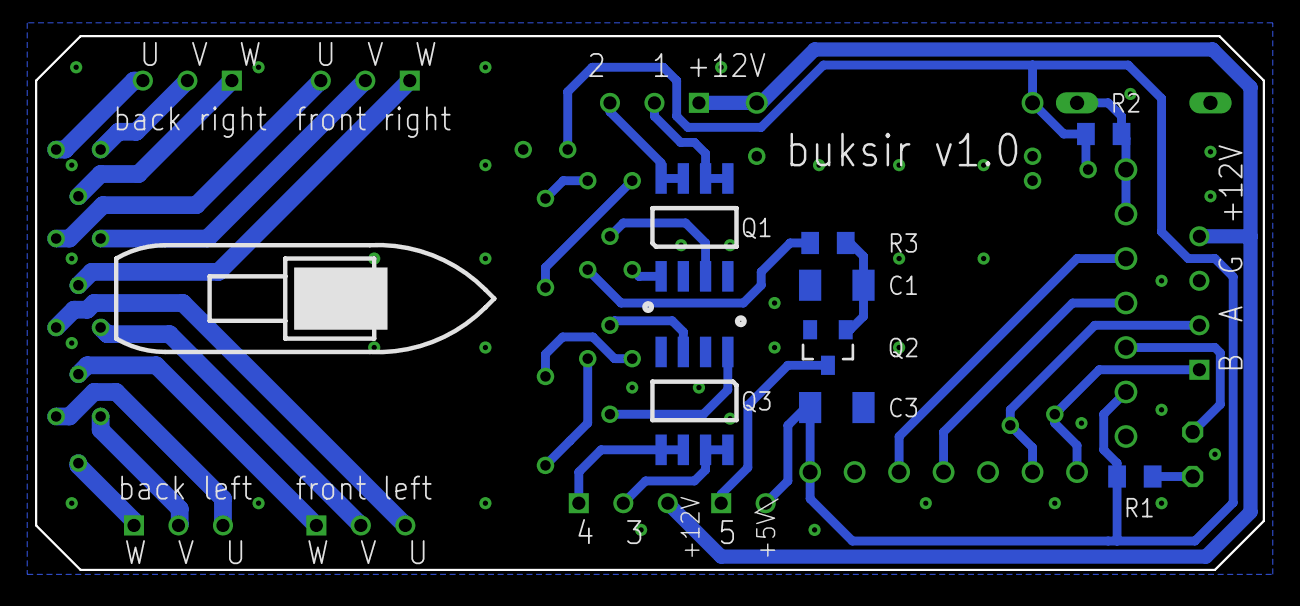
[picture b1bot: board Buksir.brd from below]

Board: 2 copper layers, 70.1 x 30.5 mm, 23 parts (8 on the bottom side), 37 nets.

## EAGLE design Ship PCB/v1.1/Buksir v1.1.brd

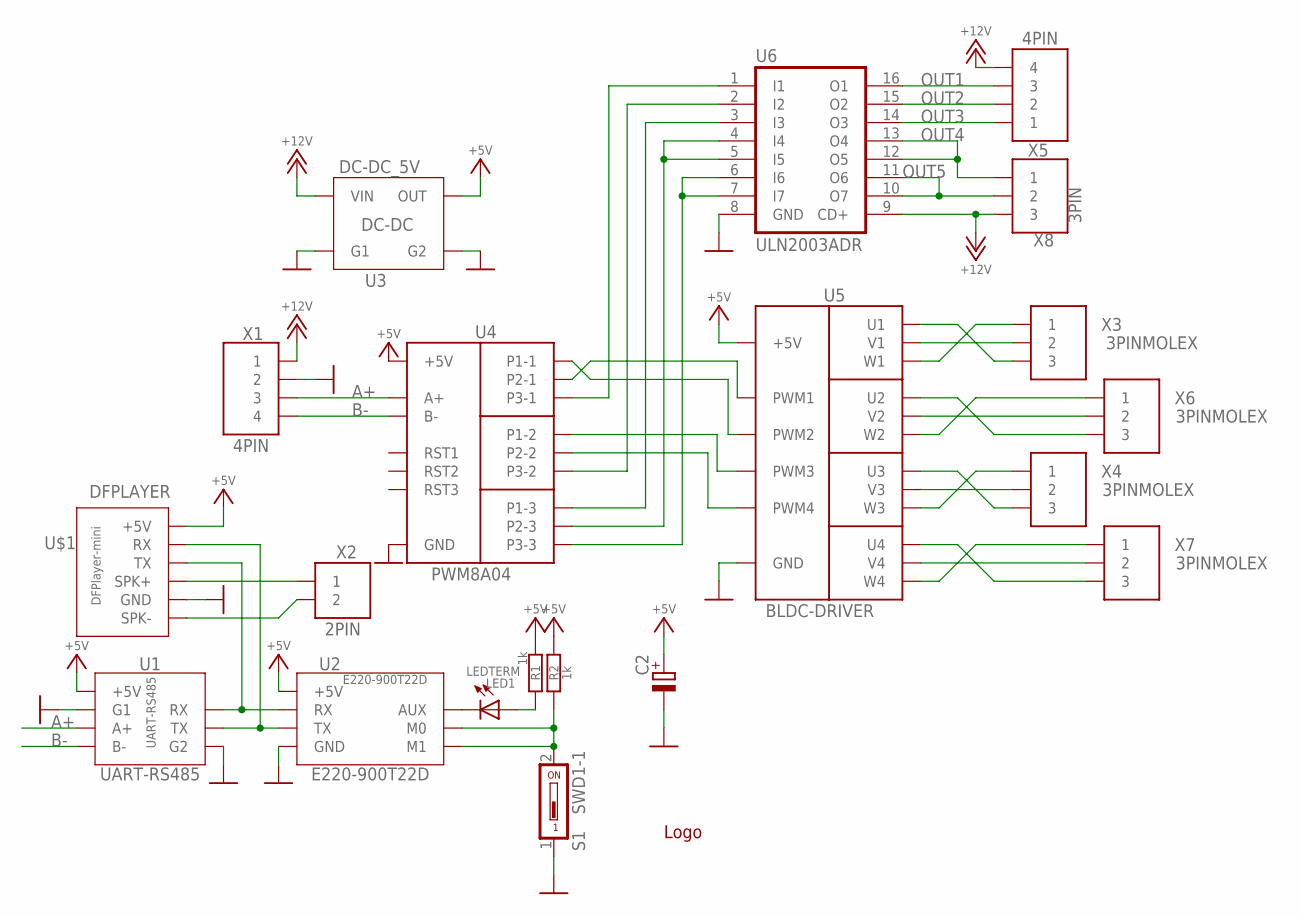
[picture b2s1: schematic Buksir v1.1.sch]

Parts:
C2: CAP_POL12; E3.5-8_R
LED1: LEDTERM; LED_TERM
R1, R2: 1k; R0805
S1: SWD1-1; DS-01
U1: UART-RS485
U2: E220-900T22D
U3: DC-DC_5V
U4: PWM8A04
U5: BLDC-DRIVER
U6: ULN2003ADR; SOIC-16
U$1: DFPLAYER; MP3-PLAYER
U$2: LOGO
X1, X5: 4PIN; 4PIN-2.5MM
X2: 2PIN; 2PIN-2.5MM
X3, X4, X6, X7: 3PINMOLEX; 3PIN-MOLEX
X8: 3PIN; 3PIN-2.5MM

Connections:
+5V: C2.+, R1.2, R2.2, U1.VCC (+5V), U2.VCC (+5V), U3.OUT, U4.+V (+5V), U5.B+ (+5V), U$1.VCC (+5V)
A+: U1.A+, U4.A+, X1.P$2 (3)
B-: U1.B-, U4.B-, X1.P$1 (4)
GND: C2.-, S1.1, U1.G1, U1.G2, U2.GND, U3.G1, U3.G2, U4.GND, U5.B- (GND), U6.8 (GND), U$1.GND, X1.P$3 (2)
unnamed: U4.P3-2, U6.2 (I2)
unnamed: U1.TX, U2.TXD (TX), U$1.RX
unnamed: LED1.K (C), U2.AUX
unnamed: LED1.A, R1.1
unnamed: R2.1, S1.2, U2.M0, U2.M1
unnamed: U4.P2-2, U5.PWM4
unnamed: U$1.S+ (SPK+), X2.P$1 (1)
unnamed: U4.P1-2, U5.PWM3
unnamed: U4.P1-1, U5.PWM2
unnamed: U5.U1, X3.P$3 (3)
unnamed: U5.V1, X3.P$2 (2)
unnamed: U5.W1, X3.P$1 (1)
unnamed: U5.W2, X6.P$1 (1)
unnamed: U5.U2, X6.P$3 (3)
unnamed: U5.V2, X6.P$2 (2)
unnamed: U5.W3, X4.P$1 (1)
unnamed: U5.U3, X4.P$3 (3)
unnamed: U5.V3, X4.P$2 (2)
unnamed: U5.U4, X7.P$3 (3)
unnamed: U5.W4, X7.P$1 (1)
unnamed: U5.V4, X7.P$2 (2)
unnamed: U4.P2-1, U5.PWM1
unnamed: U4.P1-3, U6.3 (I3)
unnamed: U$1.S- (SPK-), X2.P$2 (2)
unnamed: U1.RX, U2.RXD (RX), U$1.TX
OUT1: U6.16 (O1), X5.P$2 (3)
OUT2: U6.15 (O2), X5.P$3 (2)
OUT3: U6.14 (O3), X5.P$4 (1)
OUT4: U6.12 (O5), U6.13 (O4), X8.P$1 (1)
OUT5: U6.10 (O7), U6.11 (O6), X8.P$2 (2)
P3-1: U4.P3-1, U6.1 (I1)
P3-2: U4.P2-3, U6.4 (I4), U6.5 (I5)
P3-3: U4.P3-3, U6.6 (I6), U6.7 (I7)
V_IN: U3.VIN, U6.9 (CD+), X1.P$4 (1), X5.P$1 (4), X8.P$3 (3)

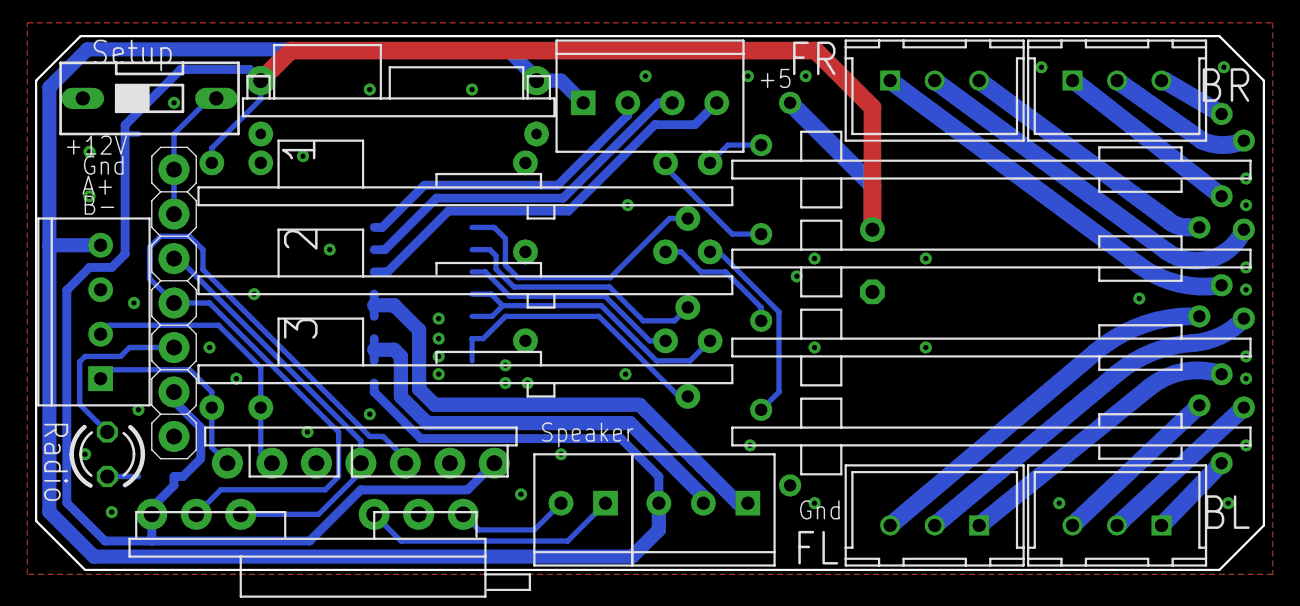
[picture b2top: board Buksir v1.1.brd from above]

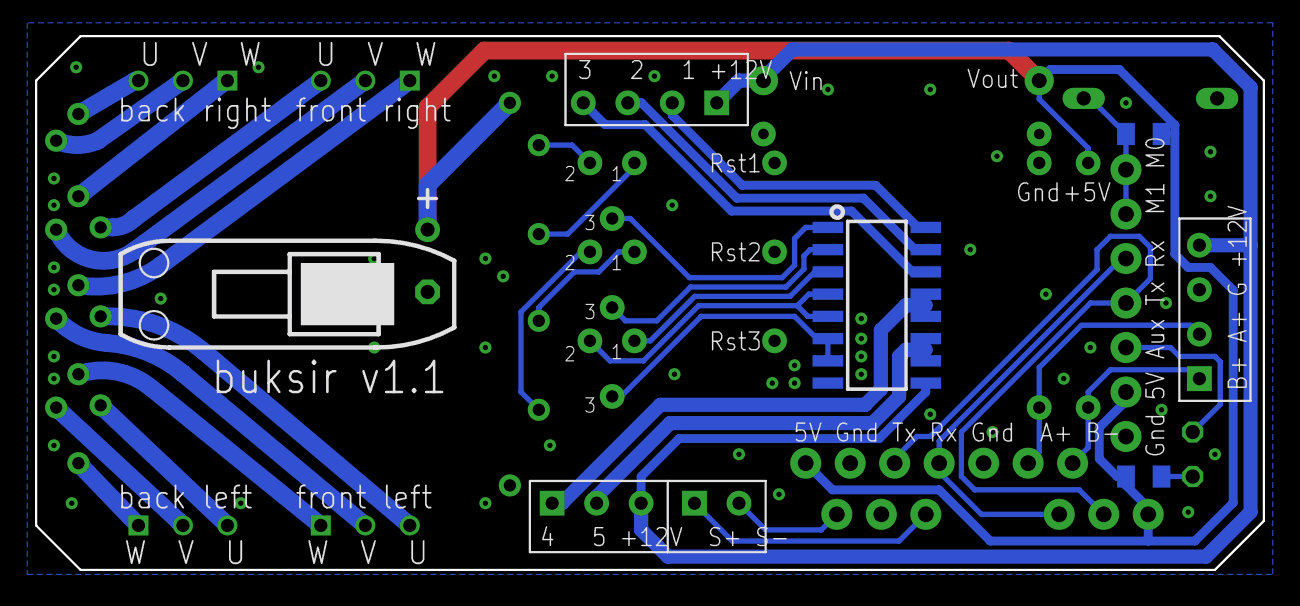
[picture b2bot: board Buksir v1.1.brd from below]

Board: 2 copper layers, 70.1 x 30.5 mm, 21 parts (5 on the bottom side), 38 nets.

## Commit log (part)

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2026-06-25 Set apt source URL to ilya-koptev.github.io
2026-06-26 Update VERSION
2026-06-28 Add Ship PCB folder: finished EAGLE boards v1.0 and v1.1 (schematic+board) + v1.1 BOM
2026-06-28 BUILD.md: now just a pointer to Ship PCB/v1.1/BOM.md (real BOM lives with the board)

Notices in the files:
README.md:
[MIT](LICENSE) © 2026 Ilya Koptev
